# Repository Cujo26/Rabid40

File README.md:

# Rabid40
40% keyboard with HHKB inspiration - first attempt at a board

Thanks to Fe, Smollchungus and Tradesplatter for all the PCB design tips and advice

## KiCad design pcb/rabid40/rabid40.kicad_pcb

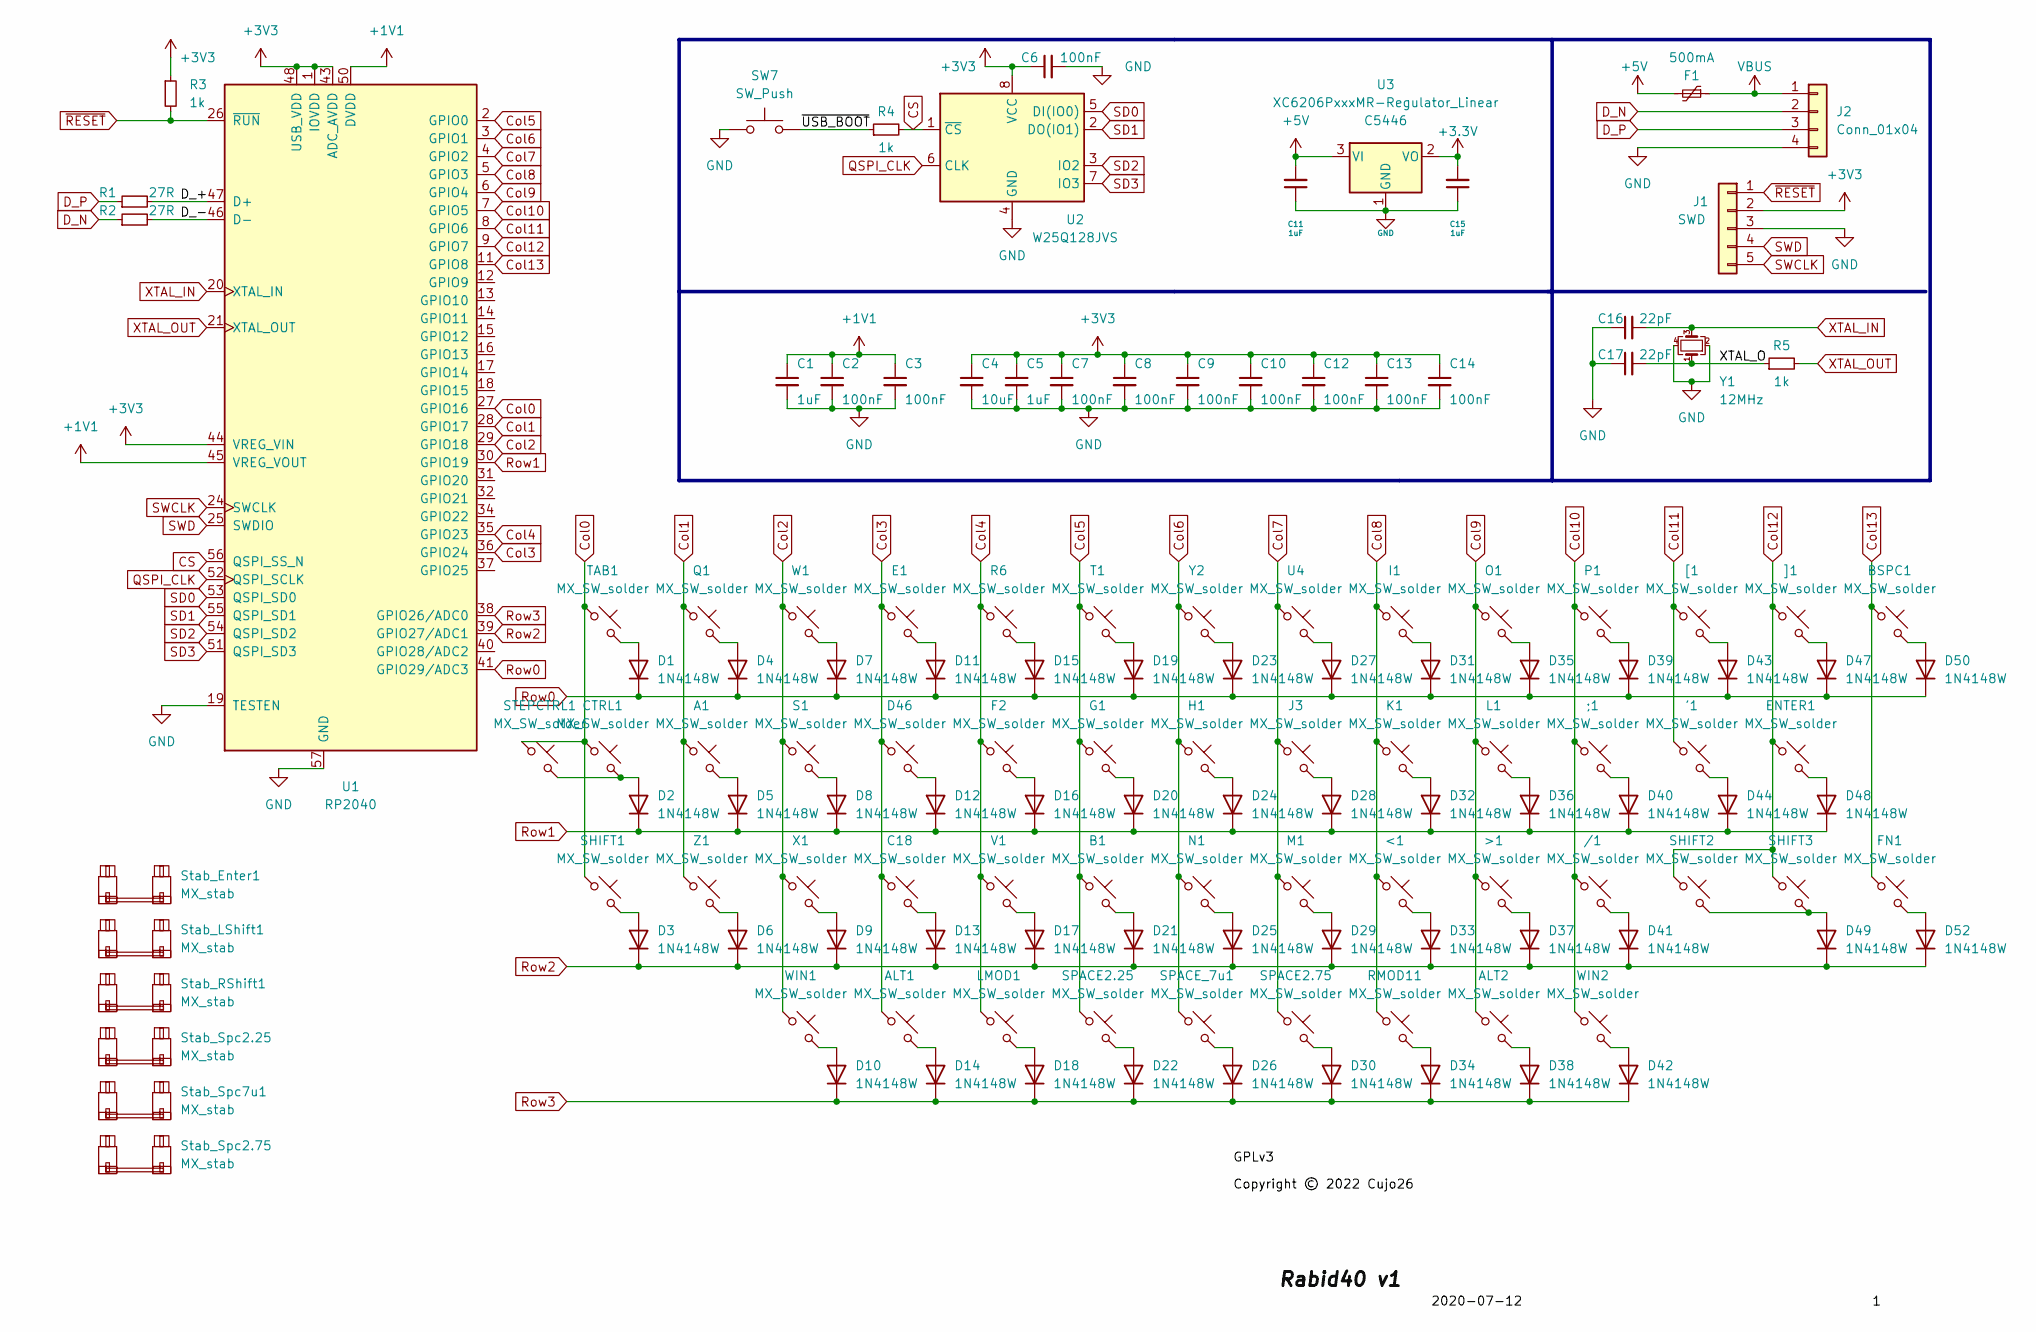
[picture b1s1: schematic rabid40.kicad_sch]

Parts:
'1: MX_SW_solder; SW_MX_1u
/1: MX_SW_solder; SW_MX_1u
;1: MX_SW_solder; SW_MX_1u
<1: MX_SW_solder; SW_MX_1u
>1: MX_SW_solder; SW_MX_1u
A1: MX_SW_solder; SW_MX_1u
ALT1, ALT2: MX_SW_solder; SW_MX_1u
B1: MX_SW_solder; SW_MX_1u
BSPC1: MX_SW_solder; SW_MX_1.5u
C1, C5, C11, C15: 1uF; C_0402_1005Metric; LCSC C52923
C2, C3, C6, C7, C8, C9, C10, C12, C13, C14: 100nF; C_0402_1005Metric; LCSC C1525
C4: 10uF; C_0402_1005Metric; LCSC C15525
C16, C17: 22pF; C_0402_1005Metric; LCSC C1555
C18: MX_SW_solder; SW_MX_1u
CTRL1: MX_SW_solder; SW_MX_1.75u
D1, D2, D3, D4, D5, D6, D7, D8, D9, D10, D11, D12, D13, D14, D15, D16, D17, D18, D19, D20, D21, D22, D23, D24, D25, D26, D27, D28, D29, D30, D31, D32, D33, D34, D35, D36, D37, D38, D39, D40, D41, D42, D43, D44, D47, D48, D49, D50, D52: 1N4148W; D_SOD-123
D46: MX_SW_solder; SW_MX_1u
E1: MX_SW_solder; SW_MX_1u
ENTER1: MX_SW_solder; SW_MX_1u
F1: 500mA; Fuse_1206_3216Metric; LCSC C70076
F2: MX_SW_solder; SW_MX_1u
FN1: MX_SW_solder; SW_MX_1u
G1: MX_SW_solder; SW_MX_1u
H1: MX_SW_solder; SW_MX_1u
I1: MX_SW_solder; SW_MX_1u
J1: SWD; PinSocket_1x05_P2.54mm_Vertical
J2: Conn_01x04; JST_SH_SM04B-SRSS-TB_1x04-1MP_P1.00mm_Horizontal
J3: MX_SW_solder; SW_MX_1u
K1: MX_SW_solder; SW_MX_1u
L1: MX_SW_solder; SW_MX_1u
LMOD1: MX_SW_solder; SW_MX_1u
M1: MX_SW_solder; SW_MX_1u
N1: MX_SW_solder; SW_MX_1u
O1: MX_SW_solder; SW_MX_1u
P1: MX_SW_solder; SW_MX_1u
Q1: MX_SW_solder; SW_MX_1u
R1, R2: 27R; R_0603_1608Metric; LCSC C25190
R3, R4, R5: 1k; R_0402_1005Metric; LCSC C11702
R6: MX_SW_solder; SW_MX_1u
RMOD11: MX_SW_solder; SW_MX_1u
S1: MX_SW_solder; SW_MX_1u
SHIFT1, SHIFT2, SHIFT3: MX_SW_solder; SW_MX_1u
SPACE2.25, SPACE2.75: MX_SW_solder; SW_MX_1u
SPACE_7u1: MX_SW_solder; SW_MX_1u
STEPCTRL1: MX_SW_solder; SW_MX_1.75u_stp
SW7: SW_Push; PinSocket_1x02_P2.54mm_Vertical
Stab_Enter1: MX_stab; STAB_MX_2.25u
Stab_LShift1: MX_stab; STAB_MX_2.25u
Stab_RShift1: MX_stab; STAB_MX_2.75u
Stab_Spc2.25: MX_stab; STAB_MX_P_2.25u
Stab_Spc2.75: MX_stab; STAB_MX_P_2.75u
Stab_Spc7u1: MX_stab; STAB_MX_P_7u
T1: MX_SW_solder; SW_MX_1u
TAB1: MX_SW_solder; SW_MX_1.5u
U1: RP2040; RP2040-QFN-56; LCSC C2040
U2: W25Q128JVS; SOIC-8_5.23x5.23mm_P1.27mm; LCSC C131025
U3: XC6206PxxxMR-Regulator_Linear; SOT-23; LCSC C5446
U4: MX_SW_solder; SW_MX_1u
V1: MX_SW_solder; SW_MX_1u
W1: MX_SW_solder; SW_MX_1u
WIN1, WIN2: MX_SW_solder; SW_MX_1u
X1: MX_SW_solder; SW_MX_1u
Y1: 12MHz; Crystal_SMD_3225-4Pin_3.2x2.5mm; LCSC C9002
Y2: MX_SW_solder; SW_MX_1u
Z1: MX_SW_solder; SW_MX_1u
[1: MX_SW_solder; SW_MX_1u
]1: MX_SW_solder; SW_MX_1u

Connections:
+1V1: C1.1, C2.1, C3.1, U1.23 (DVDD), U1.45 (VREG_VOUT), U1.50 (DVDD)
+5V: C11.2, F1.2, U3.3 (VI)
/D_+: R1.2, U1.47 (D+)
/D_-: R2.2, U1.46 (D-)
/XTAL_O: C17.2, R5.1, Y1.1
/~USB_BOOT: R4.1, SW7.2
CS: R4.2, U1.56 (QSPI_SS_N), U2.1 (~CS)
Col0: CTRL1.1, SHIFT1.1, STEPCTRL1.1, TAB1.1, U1.27 (GPIO16)
Col1: A1.1, Q1.1, U1.28 (GPIO17), Z1.1
Col2: S1.1, U1.29 (GPIO18), W1.1, WIN1.1, X1.1
Col3: ALT1.1, C18.1, D46.1, E1.1, U1.36 (GPIO24)
Col4: F2.1, LMOD1.1, R6.1, U1.35 (GPIO23), V1.1
Col5: B1.1, G1.1, SPACE2.25.1, T1.1, U1.2 (GPIO0)
Col6: H1.1, N1.1, SPACE_7u1.1, U1.3 (GPIO1), Y2.1
Col7: J3.1, M1.1, SPACE2.75.1, U1.4 (GPIO2), U4.1
Col8: <1.1, I1.1, K1.1, RMOD11.1, U1.5 (GPIO3)
Col9: >1.1, ALT2.1, L1.1, O1.1, U1.6 (GPIO4)
Col10: /1.1, ;1.1, P1.1, U1.7 (GPIO5), WIN2.1
Col11: '1.1, U1.8 (GPIO6), [1.1
Col12: ENTER1.1, SHIFT2.1, SHIFT3.1, U1.9 (GPIO7), ]1.1
Col13: BSPC1.1, FN1.1, U1.11 (GPIO8)
D_N: J2.2, R2.1
D_P: J2.3, R1.1
GND: C1.2, C2.2, C3.2, C4.2, C5.2, C6.2, C7.2, C8.2, C9.2, C10.2, C11.1, C12.2, C13.2, C14.2, C15.1, C16.1, C17.1, J1.3, J2.4, SW7.1, U1.19 (TESTEN), U1.57 (GND), U2.4 (GND), U3.1 (GND), Y1.2, Y1.4
unnamed: '1.2, D44.2 (A)
unnamed: /1.2, D41.2 (A)
unnamed: ;1.2, D40.2 (A)
unnamed: <1.2, D33.2 (A)
unnamed: >1.2, D37.2 (A)
unnamed: A1.2, D5.2 (A)
unnamed: ALT1.2, D14.2 (A)
unnamed: B1.2, D21.2 (A)
unnamed: BSPC1.2, D50.2 (A)
unnamed: C18.2, D13.2 (A)
unnamed: CTRL1.2, D2.2 (A), STEPCTRL1.2
unnamed: D1.2 (A), TAB1.2
unnamed: D3.2 (A), SHIFT1.2
unnamed: D4.2 (A), Q1.2
unnamed: D6.2 (A), Z1.2
unnamed: D7.2 (A), W1.2
unnamed: D8.2 (A), S1.2
unnamed: D9.2 (A), X1.2
unnamed: D10.2 (A), WIN1.2
unnamed: D11.2 (A), E1.2
unnamed: D12.2 (A), D46.2
unnamed: D15.2 (A), R6.2
unnamed: D16.2 (A), F2.2
unnamed: D17.2 (A), V1.2
unnamed: D18.2 (A), LMOD1.2
unnamed: D19.2 (A), T1.2
unnamed: D20.2 (A), G1.2
unnamed: D22.2 (A), SPACE2.25.2
unnamed: D23.2 (A), Y2.2
unnamed: D24.2 (A), H1.2
unnamed: D25.2 (A), N1.2
unnamed: D26.2 (A), SPACE_7u1.2
unnamed: D27.2 (A), U4.2
unnamed: D28.2 (A), J3.2
unnamed: D29.2 (A), M1.2
unnamed: D30.2 (A), SPACE2.75.2
unnamed: D31.2 (A), I1.2
unnamed: D32.2 (A), K1.2
unnamed: D34.2 (A), RMOD11.2
unnamed: D35.2 (A), O1.2
unnamed: D36.2 (A), L1.2
unnamed: D39.2 (A), P1.2
unnamed: D42.2 (A), WIN2.2
unnamed: D43.2 (A), [1.2
unnamed: D47.2 (A), ]1.2
unnamed: D48.2 (A), ENTER1.2
unnamed: D49.2 (A), SHIFT2.2, SHIFT3.2
unnamed: D52.2 (A), FN1.2
QSPI_CLK: U1.52 (QSPI_SCLK), U2.6 (CLK)
Row0: D1.1 (K), D4.1 (K), D7.1 (K), D11.1 (K), D15.1 (K), D19.1 (K), D23.1 (K), D27.1 (K), D31.1 (K), D35.1 (K), D39.1 (K), D43.1 (K), D47.1 (K), D50.1 (K), U1.41 (GPIO29/ADC3)
Row1: D2.1 (K), D5.1 (K), D8.1 (K), D12.1 (K), D16.1 (K), D20.1 (K), D24.1 (K), D28.1 (K), D32.1 (K), D36.1 (K), D40.1 (K), D44.1 (K), D48.1 (K), U1.30 (GPIO19)
Row2: D3.1 (K), D6.1 (K), D9.1 (K), D13.1 (K), D17.1 (K), D21.1 (K), D25.1 (K), D29.1 (K), D33.1 (K), D37.1 (K), D41.1 (K), D49.1 (K), D52.1 (K), U1.39 (GPIO27/ADC1)
Row3: D10.1 (K), D14.1 (K), D18.1 (K), D22.1 (K), D26.1 (K), D30.1 (K), D34.1 (K), D38.1 (K), D42.1 (K), U1.38 (GPIO26/ADC0)
SD0: U1.53 (QSPI_SD0), U2.5 (DI(IO0))
SD1: U1.55 (QSPI_SD1), U2.2 (DO(IO1))
SD2: U1.54 (QSPI_SD2), U2.3 (IO2)
SD3: U1.51 (QSPI_SD3), U2.7 (IO3)
SWCLK: J1.5, U1.24 (SWCLK)
SWD: J1.4, U1.25 (SWDIO)
VBUS: F1.1, J2.1
XTAL_IN: C16.2, U1.20 (XTAL_IN), Y1.3
XTAL_OUT: R5.2, U1.21 (XTAL_OUT)
~RESET: J1.1, R3.2, U1.26 (~RUN)

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
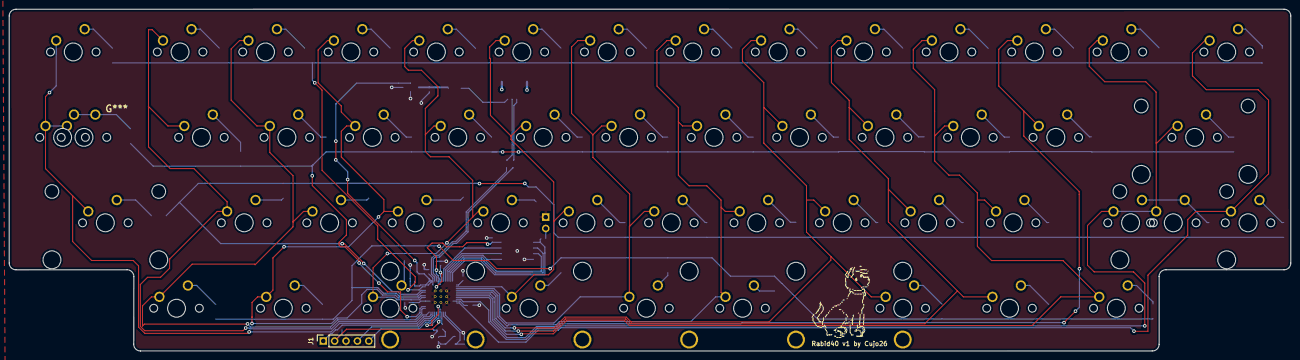
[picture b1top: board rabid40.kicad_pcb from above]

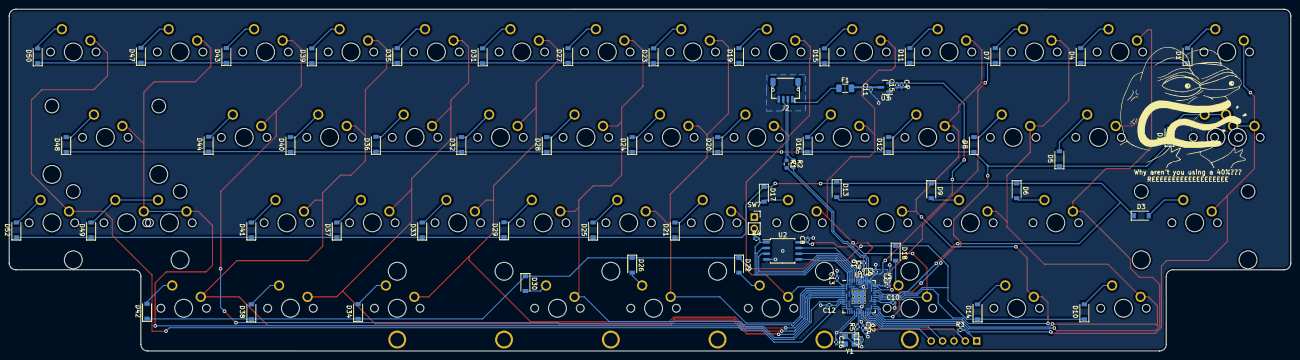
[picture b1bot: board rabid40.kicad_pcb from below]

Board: 2 copper layers, 285.8 x 76.2 mm, 136 parts (78 on the bottom side), 88 nets.

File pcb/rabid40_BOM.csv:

"Id";"Designator";"Package";"Quantity";"Designation";"Supplier and ref";
1;"J2";"JST_EH_S4B-EH_1x04_P2.50mm_Horizontal";1;"Conn_01x04";;;
2;"F2,P1,Q1,W1,G1,D46,E1,;1,T1,J3,Win1,H1,<1,U4,L1,[1,I1,V1,Shift3,Space_7u1,Y2,Shift2,Space2.25,Space2.75,Fn1,B1,Shift1,M1,Z1,C18,S1,A1,'1,X1,/1,R6,RMod1,K1,Win2,>1,N1,]1,Enter1,O1,LMod1";"SW_MX_1u";45;"MX_SW_solder";;;
3;"Stab_Enter1,Stab_LShift1";"STAB_MX_2.25u";2;"MX_stab";;;
4;"Stab_Spc2.25";"STAB_MX_P_2.25u";1;"MX_stab";;;
5;"Stab_Spc7u1";"STAB_MX_P_7u";1;"MX_stab";;;
6;"Tab1,Bspc1";"SW_MX_1.5u";2;"MX_SW_solder";;;
7;"StepCtrl1";"SW_MX_1.75u_stp";1;"MX_SW_solder";;;
8;"Ctrl1";"SW_MX_1.75u";1;"MX_SW_solder";;;
9;"Stab_Spc2.75";"STAB_MX_P_2.75u";1;"MX_stab";;;
10;"Stab_RShift1";"STAB_MX_2.75u";1;"MX_stab";;;
11;"C11,C5,C15,C1";"C_0402_1005Metric";4;"1uF";;;
12;"D32,D1,D20,D44,D39,D15,D26,D4,D10,D24,D28,D49,D3,D17,D47,D42,D50,D8,D48,D34,D30,D23,D41,D9,D12,D43,D29,D36,D25,D14,D52,D6,D40,D19,D2,D18,D5,D21,D31,D16,D27,D13,D35,D38,D11,D33,D22,D7,D37";"D_SOD-123";49;"1N4148W";;;
13;"U1";"RP2040-QFN-56";1;"RP2040";;;
14;"C6,C2,C7,C10,C13,C8,C14,C3,C9,C12";"C_0402_1005Metric";10;"100nF";;;
15;"R4,R5,R3";"R_0402_1005Metric";3;"1k";;;
16;"C4";"C_0402_1005Metric";1;"10uF";;;
17;"U2";"SOIC-8_5.23x5.23mm_P1.27mm";1;"W25Q128JVS";;;
18;"U3";"SOT-23";1;"XC6206PxxxMR-Regulator_Linear";;;
19;"Y1";"Crystal_SMD_3225-4Pin_3.2x2.5mm";1;"12MHz";;;
20;"R1,R2";"R_0603_1608Metric";2;"27R";;;
21;"F1";"Fuse_1206_3216Metric";1;"500mA";;;
22;"C17,C16";"C_0402_1005Metric";2;"22pF";;;

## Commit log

2022-06-27 committed submodules and initial kicad project
2022-06-27 added mx alps libs
2022-06-27 schematic basics laid down
2022-06-27 components pooped out onto pcb
2022-06-28 all components added for the 40
2022-06-28 basic routing
2022-06-28 added multilayout support to schematic
2022-06-28 more switches aligned
2022-06-29 switches in order, mcu components near their place
2022-06-30 repositioned capacitors
2022-07-12 reset schematic, added submodules
2022-07-12 files organised
2022-07-13 matrix more or less organised
2022-07-13 moved some mcu components into place
2022-08-09 started placing traces, its very scuff
2022-08-10 completed routing
2022-08-10 finished routing
2022-08-10 added annotationos
2022-08-10 pcb updated with feedback from tradesplatter. Gerbers regenerated
2022-08-10 missed a spot
2022-08-10 generated BOM and zipped gerbers
2022-08-11 added branding
2022-08-15 added backplane, fixed header breakout
2022-08-16 fixed some issues to make it manufacturable at jlcpcb
2022-08-17 added meme
2022-08-17 new gerbers and drill files
2022-08-30 minor updates
